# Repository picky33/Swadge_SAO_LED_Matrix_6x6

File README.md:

# Swadge_SAO_LED_Matrix_6x6
6x6 version and square version of LED Maxtrix

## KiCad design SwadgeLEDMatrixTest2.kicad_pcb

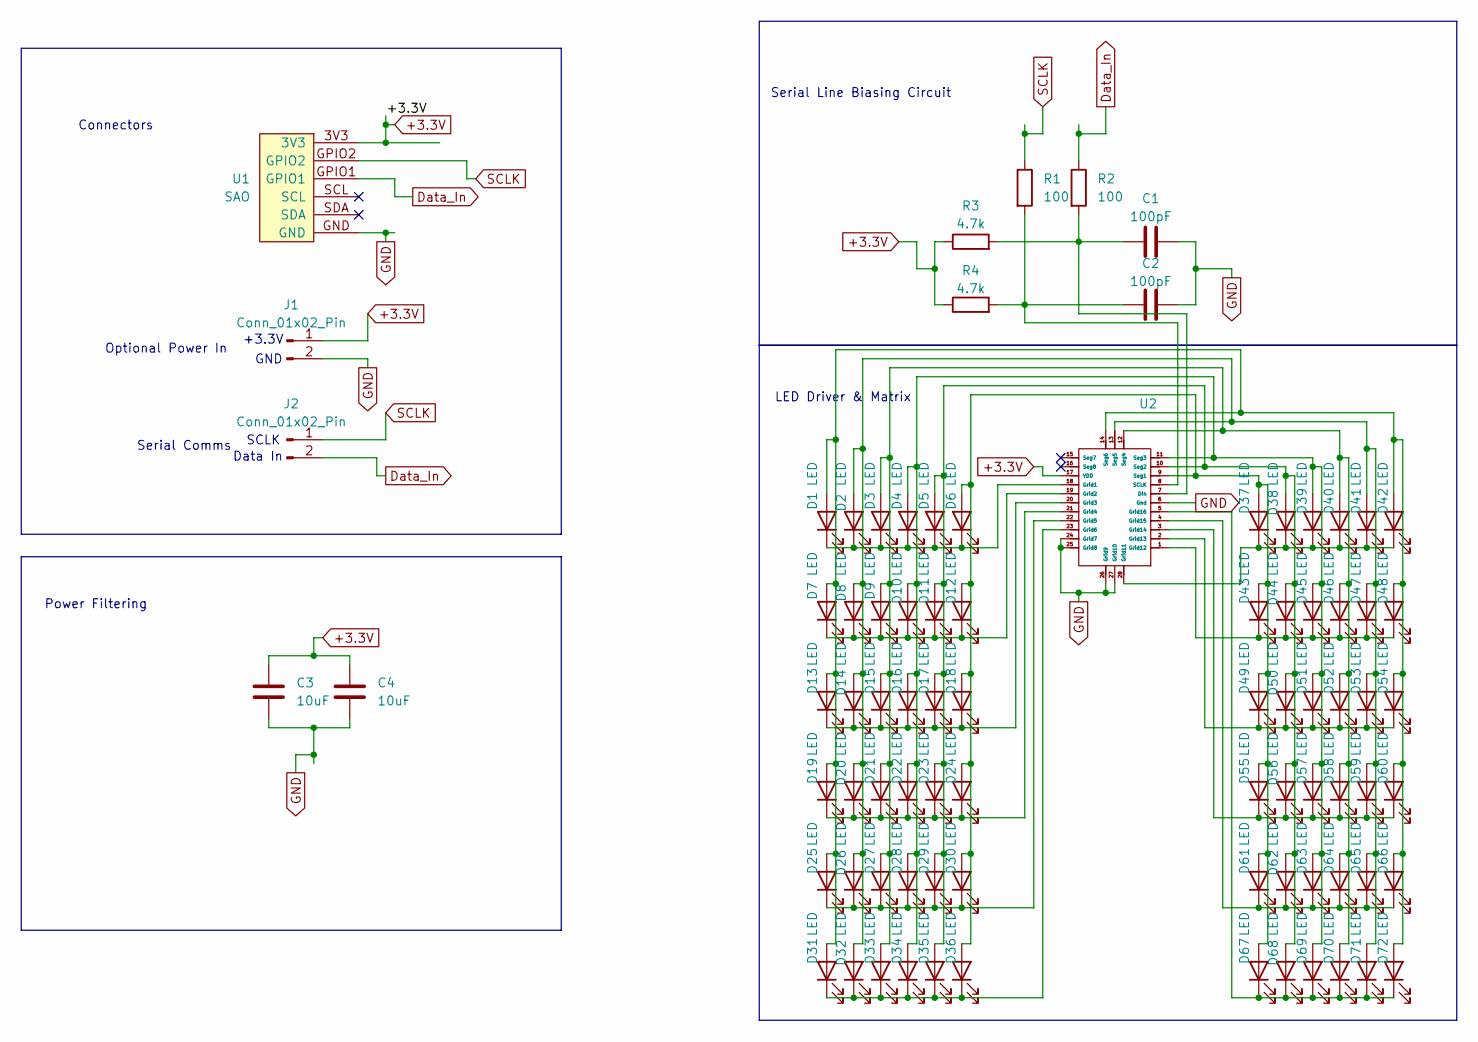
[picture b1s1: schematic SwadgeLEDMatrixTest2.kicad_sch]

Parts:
C1, C2: 100pF; C_0805_2012Metric_Pad1.18x1.45mm_HandSolder
C3, C4: 10uF; C_0805_2012Metric_Pad1.18x1.45mm_HandSolder
D1, D2, D3, D4, D5, D6, D7, D8, D9, D10, D11, D12, D13, D14, D15, D16, D17, D18, D19, D20, D21, D22, D23, D24, D25, D26, D27, D28, D29, D30, D31, D32, D33, D34, D35, D36, D37, D38, D39, D40, D41, D42, D43, D44, D45, D46, D47, D48, D49, D50, D51, D52, D53, D54, D55, D56, D57, D58, D59, D60, D61, D62, D63, D64, D65, D66, D67, D68, D69, D70, D71, D72: LED; LED_0603_1608Metric_Pad1.05x0.95mm_HandSolder
J1, J2: Conn_01x02_Pin; PinHeader_1x02_P2.54mm_Vertical
R1, R2: 100; R_0805_2012Metric_Pad1.20x1.40mm_HandSolder
R3, R4: 4.7k; R_0805_2012Metric_Pad1.20x1.40mm_HandSolder
U1: SAO; Digikey n/a
U2: EP1640

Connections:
+3.3V: C3.1, C4.1, J1.1, R3.1, R4.1, U1.3V3, U2.17 (VDD)
Data_In: J2.2, R2.1, U1.GPIO1
GND: C1.2, C2.2, C3.2, C4.2, J1.2, U1.GND, U2.6 (Gnd), U2.24 (Grid7), U2.25 (Grid8), U2.26 (Grid9), U2.27 (Grid10)
unnamed: D1.2 (A), D7.2 (A), D13.2 (A), D19.2 (A), D25.2 (A), D31.2 (A), D42.2 (A), D48.2 (A), D54.2 (A), D60.2 (A), D66.2 (A), D72.2 (A), U2.14 (Seg6)
unnamed: D1.1 (K), D2.1 (K), D3.1 (K), D4.1 (K), D5.1 (K), D6.1 (K), U2.18 (Grid1)
unnamed: D4.2 (A), D10.2 (A), D16.2 (A), D22.2 (A), D28.2 (A), D34.2 (A), D39.2 (A), D45.2 (A), D51.2 (A), D57.2 (A), D63.2 (A), D69.2 (A), U2.11 (Seg3)
unnamed: D7.1 (K), D8.1 (K), D9.1 (K), D10.1 (K), D11.1 (K), D12.1 (K), U2.19 (Grid2)
unnamed: D5.2 (A), D11.2 (A), D17.2 (A), D23.2 (A), D29.2 (A), D35.2 (A), D38.2 (A), D44.2 (A), D50.2 (A), D56.2 (A), D62.2 (A), D68.2 (A), U2.10 (Seg2)
unnamed: D6.2 (A), D12.2 (A), D18.2 (A), D24.2 (A), D30.2 (A), D36.2 (A), D37.2 (A), D43.2 (A), D49.2 (A), D55.2 (A), D61.2 (A), D67.2 (A), U2.9 (Seg1)
unnamed: D13.1 (K), D14.1 (K), D15.1 (K), D16.1 (K), D17.1 (K), D18.1 (K), U2.20 (Grid3)
unnamed: D2.2 (A), D8.2 (A), D14.2 (A), D20.2 (A), D26.2 (A), D32.2 (A), D41.2 (A), D47.2 (A), D53.2 (A), D59.2 (A), D65.2 (A), D71.2 (A), U2.13 (Seg5)
unnamed: D3.2 (A), D9.2 (A), D15.2 (A), D21.2 (A), D27.2 (A), D33.2 (A), D40.2 (A), D46.2 (A), D52.2 (A), D58.2 (A), D64.2 (A), D70.2 (A), U2.12 (Seg4)
unnamed: D19.1 (K), D20.1 (K), D21.1 (K), D22.1 (K), D23.1 (K), D24.1 (K), U2.21 (Grid4)
unnamed: D25.1 (K), D26.1 (K), D27.1 (K), D28.1 (K), D29.1 (K), D30.1 (K), U2.22 (Grid5)
unnamed: D31.1 (K), D32.1 (K), D33.1 (K), D34.1 (K), D35.1 (K), D36.1 (K), U2.23 (Grid6)
unnamed: D37.1 (K), D38.1 (K), D39.1 (K), D40.1 (K), D41.1 (K), D42.1 (K), U2.28 (Grid11)
unnamed: D43.1 (K), D44.1 (K), D45.1 (K), D46.1 (K), D47.1 (K), D48.1 (K), U2.1 (Grid12)
unnamed: D49.1 (K), D50.1 (K), D51.1 (K), D52.1 (K), D53.1 (K), D54.1 (K), U2.2 (Grid13)
unnamed: D55.1 (K), D56.1 (K), D57.1 (K), D58.1 (K), D59.1 (K), D60.1 (K), U2.3 (Grid14)
unnamed: D61.1 (K), D62.1 (K), D63.1 (K), D64.1 (K), D65.1 (K), D66.1 (K), U2.4 (Grid15)
unnamed: D67.1 (K), D68.1 (K), D69.1 (K), D70.1 (K), D71.1 (K), D72.1 (K), U2.5 (Grid16)
unnamed: C1.1, R2.2, R3.2, U2.7 (Din)
unnamed: C2.1, R1.2, R4.2, U2.8 (SCLK)
SCLK: J2.1, R1.1, U1.GPIO2

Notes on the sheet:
Power Filtering
GND
Serial Line Biasing Circuit
+3.3V
Connectors
Serial Comms
SCLK
Optional Power In
Data In
LED Driver & Matrix

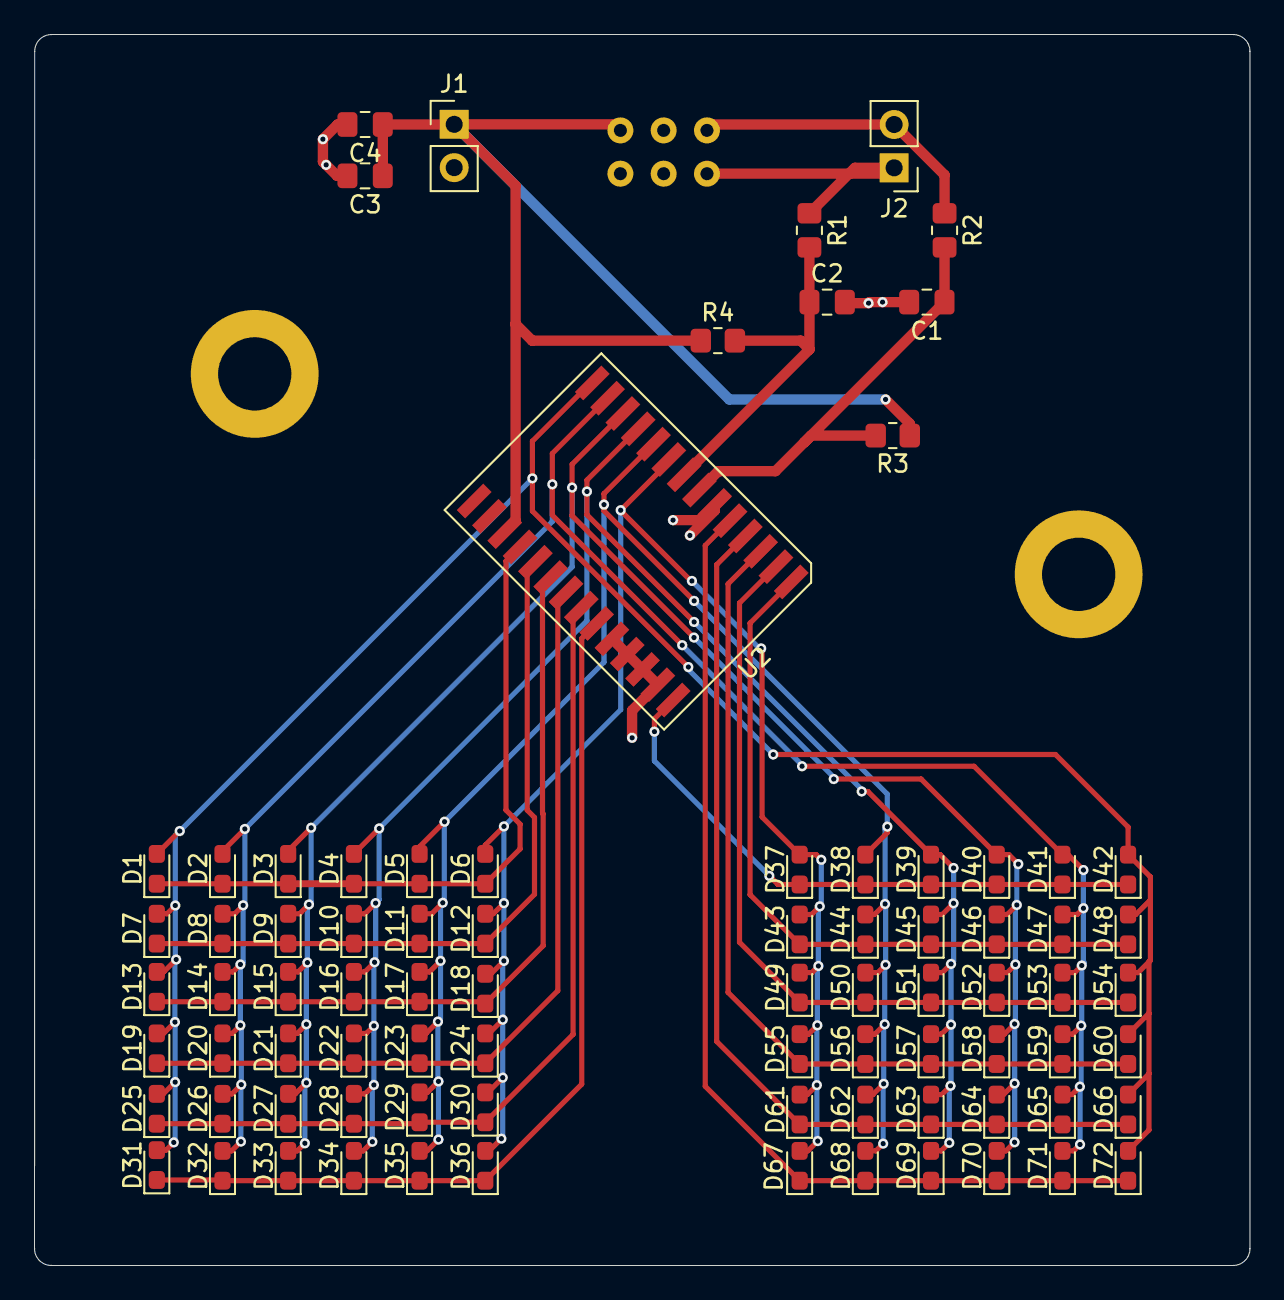
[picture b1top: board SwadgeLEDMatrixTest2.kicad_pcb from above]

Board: 2 copper layers, 71.3 x 72.2 mm, 84 parts (1 on the bottom side), 24 nets.

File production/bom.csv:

Designator,Footprint,Quantity,Value,LCSC Part #
"C1, C2",0805,2,100pF,
"C3, C4",0805,2,10uF,
"D1, D10, D11, D12, D13, D14, D15, D16, D17, D18, D19, D2, D20, D21, D22, D23, D24, D25, D26, D27, D28, D29, D3, D30, D31, D32, D33, D34, D35, D36, D37, D38, D39, D4, D40, D41, D42, D43, D44, D45, D46, D47, D48, D49, D5, D50, D51, D52, D53, D54, D55, D56, D57, D58, D59, D6, D60, D61, D62, D63, D64, D65, D66, D67, D68, D69, D7, D70, D71, D72, D8, D9",0603,72,LED,
"J1, J2",PinHeader_1x02_P2.54mm_Vertical,2,Conn_01x02_Pin,
"R1, R2",0805,2,100,
"R3, R4",0805,2,4.7k,
U1,SAO,1,SAO,
U2,EP1640,1,~,

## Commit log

2025-05-16 init
    init
2025-05-16 fabrication outputs
2025-05-16 even now
